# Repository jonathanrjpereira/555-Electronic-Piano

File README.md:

# Electronic Piano | LM555
An electronic piano that uses the 555 to generate eight different piano notes.

**Order PCB:**

## Electronic Components
| Qty | Component | Buy |
| ------------- | ------------- | ------------- |
| 1 | 555 |[AliExpress](http://s.click.aliexpress.com/e/sCv1ACC) |
| 1 | 390Ω, 620Ω, 910Ω, 1.1KΩ, 1.3KΩ, 1.5K, 2KΩ, 6.2KΩ |[AliExpress](http://s.click.aliexpress.com/e/bh4eqrQs) |
| 2 | 1KΩ Resistor |[AliExpress](http://s.click.aliexpress.com/e/bh4eqrQs) |
| 8 | Tactile Momentary Push Buttons |[AliExpress](http://s.click.aliexpress.com/e/c77Ajrpq) |
| 1 | 5mm LED |[AliExpress](http://s.click.aliexpress.com/e/wuFpLXS) |
| 1 | 0.1uF Capacitor |[AliExpress](http://s.click.aliexpress.com/e/c9FHzl5W) |
| 1 | 10nF Capacitor |[AliExpress](http://s.click.aliexpress.com/e/byQG0DZW) |
| 2 | 2 Pin Screw Terminal |[AliExpress](http://s.click.aliexpress.com/e/xYUweh2) |
| 1 | Speaker |[AliExpress](http://s.click.aliexpress.com/e/brMJh46c) |
| 1 | 9V Battery Holder |[AliExpress](http://s.click.aliexpress.com/e/c3jbp72Y) |
| 1 | 9V Battery |[AliExpress](http://s.click.aliexpress.com/e/bbDirGHE) |
| 1 | PCB |[AliExpress](http://s.click.aliexpress.com/e/dhgwzKY) |

| Tools | Buy |
|--|--|
|Soldering Iron|[AliExpress](http://s.click.aliexpress.com/e/E83bSJI) |
|Soldering Wire|[AliExpress](http://s.click.aliexpress.com/e/PdhB0nm) |
|Mini PCB Hand Drill + Bits|[AliExpress](http://s.click.aliexpress.com/e/b93tomjI) |

## Working
**LM555/NE555:**

The 555 is a highly stable device for generating accurate time delays or oscillation. Additional terminals are provided for triggering or resetting if desired. For stable operation as an oscillator, the free running frequency and duty cycle are accurate controlled with two external resistors and one capacitor. The circuit may be triggered and reset on falling waveforms, and he output circuit can source or sink up to 200mA or drive TTL circuits.

**Circuit:**

The circuit is connected such that it will trigger itself and free run as an astable multivibrator. The external capacitor charges through Ra+Rb and discharges through Rb. Thus th duty cycle may be precisely set by the ratio of these two resistors.

In this mode of operation, the capacitor charges and discharges between 1/3 VCC and 2/3 VCC. Hence the charge and discharge times, and therefore the frequency are independent of the supply voltage.

The change time (output high) is given by:

And the discharge time (output low) by:

Thus the total period is:

The frequency of oscillation is:

Hence

An input trigger such as a switch or button is pressed which connects its corresponding resistance within the resistor chain to the IC 555 which acts as an Astable Multivibrator. Depending on the value of the resistance the speaker will produce a different sound.

Each piano key has a separate frequency associated with it as shown in the table below.
We have kept the values of Ra & C as constant and only vary the value of Rb in order to change the frequency whenever a different key is pressed. In order to do this we created a resistor chain according to the table above as shown in the schematic. This chain is configured to optimize and reduce the number of individual resistors required.

## Contributing🛠
Are you an engineer or hobbyist who has a great idea for a new feature in this project? Maybe you have a good idea for a bug fix? Feel free to grab our code & schematics from Github and tinker with it. Don't forget to smash ⭐️ & the Pull Request button.

[![alt text][1.1]][1] [![alt text][2.1]][2] [![alt text][3.1]][3]

[1.1]: https://github.com/jonathanrjpereira/Social-Media-README/blob/master/youtube.png (YouTube)
[2.1]: https://github.com/jonathanrjpereira/Social-Media-README/blob/master/instagram.png (Instagram)
[3.1]: https://github.com/jonathanrjpereira/Social-Media-README/blob/master/github.png (GitHub)

[1]: https://www.youtube.com/channel/UCRW-41O1vy98KKgJRQoYzdg
[2]: https://www.instagram.com/electroguruji/
[3]: https://github.com/jonathanrjpereira

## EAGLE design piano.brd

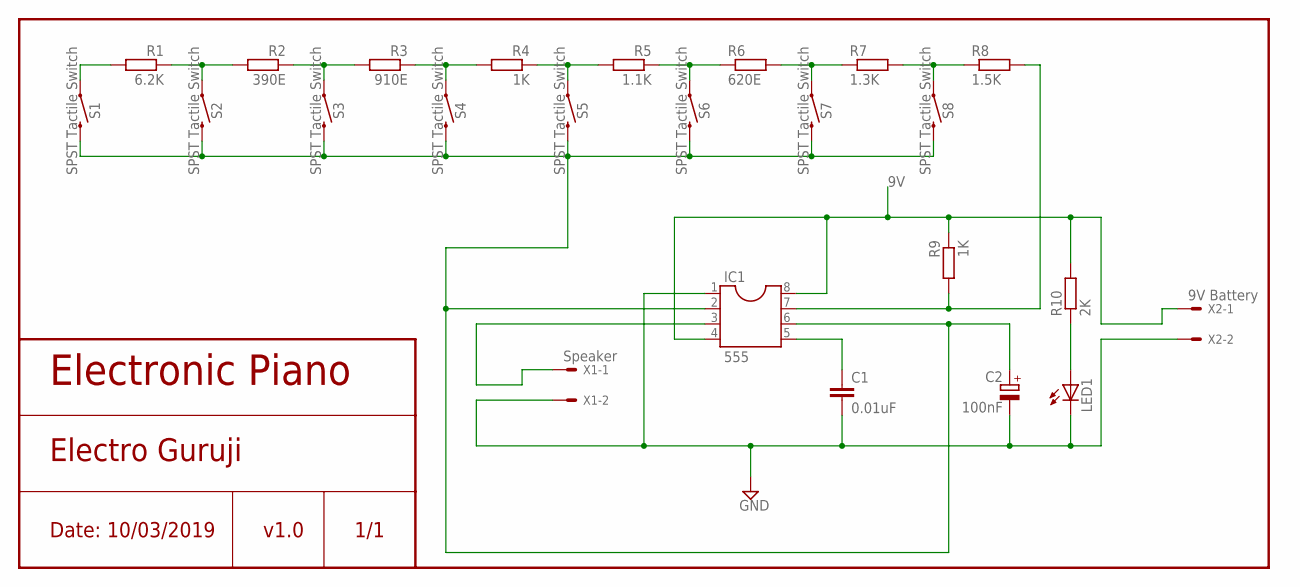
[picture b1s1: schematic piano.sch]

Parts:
C1: 0.01uF; C025-024X044
C2: 100nF; E5-5
IC1: 555; SOCKET-08
LED1: LED5MM
R1: 6.2K; 0204/5
R2: 390E; 0204/5
R3: 910E; 0204/5
R4, R9: 1K; 0204/5
R5: 1.1K; 0204/5
R6: 620E; 0204/5
R7: 1.3K; 0204/5
R8: 1.5K; 0204/5
R10: 2K; 0204/5
S1, S2, S3, S4, S5, S6, S7, S8: SPST Tactile Switch; TACTILE_SWITCH_PTH_6.0MM
X1: Speaker; KK-156-2
X2: 9V Battery; KK-156-2

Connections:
9V: IC1.4, IC1.8, R9.1, R10.2, X2.1
GND: C1.2, C2.-, IC1.1, LED1.K (C), X1.2, X2.2
unnamed: IC1.7, R8.2, R9.2
unnamed: C1.1, IC1.5
unnamed: C2.+, IC1.2, IC1.6, S1.3 (2), S2.3 (2), S3.3 (2), S4.3 (2), S5.3 (2), S6.3 (2), S7.3 (2), S8.3 (2)
unnamed: R1.2, S1.1
unnamed: R1.1, R2.2, S2.1
unnamed: R2.1, R3.2, S3.1
unnamed: R3.1, R4.2, S4.1
unnamed: R4.1, R5.2, S5.1
unnamed: R5.1, R6.1, S6.1
unnamed: R7.2, R8.1, S8.1
unnamed: R6.2, R7.1, S7.1
unnamed: IC1.3, X1.1
unnamed: LED1.A, R10.1

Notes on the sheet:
Electronic Piano
Electro Guruji
Date: 10/03/2019
v1.0
1/1

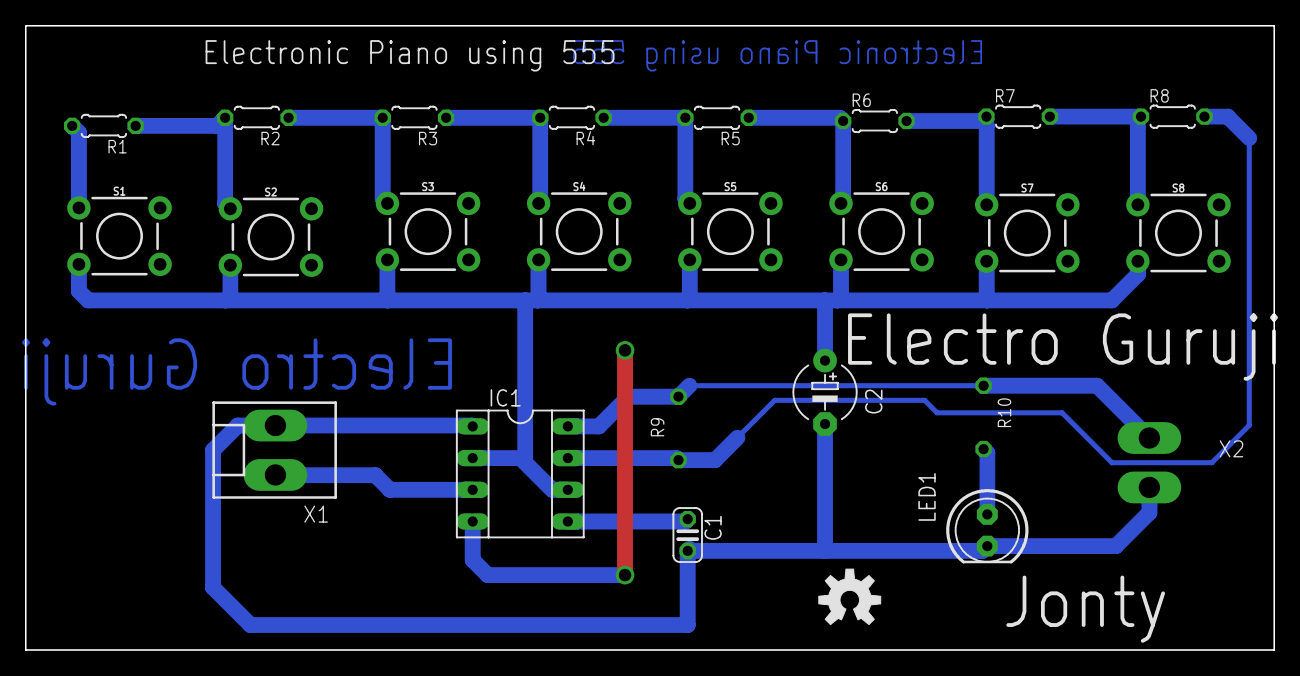
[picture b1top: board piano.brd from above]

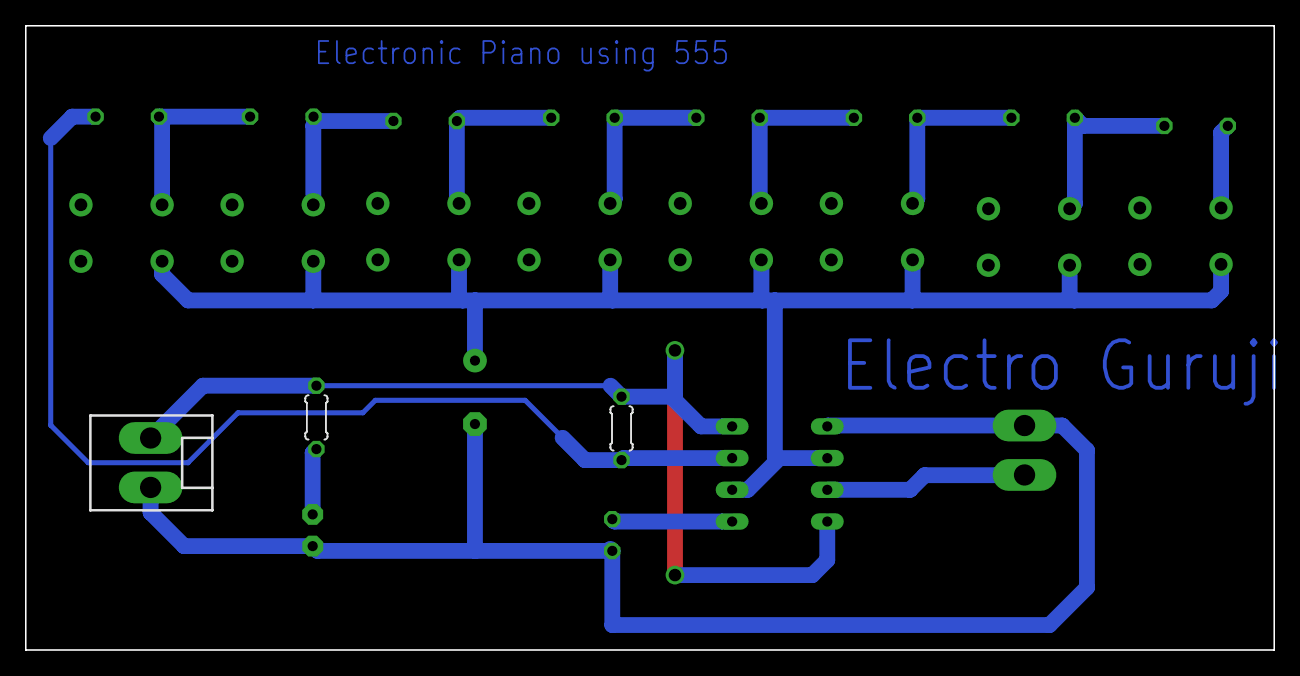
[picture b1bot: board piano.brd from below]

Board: 2 copper layers, 100.0 x 50.0 mm, 25 parts (3 on the bottom side), 15 nets.

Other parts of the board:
U$1: OSHW-LOGO-M

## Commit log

2019-03-12 All images
2019-03-12 Schematic & Board
2019-03-12 Rb Calculator
    Enter desired frequencies for fixed value of Ra & C.
    Output: Corresponding value of Rb
2019-03-12 Components, Working
2019-03-17 printable

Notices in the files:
parts and their libraries:
SparkFun-Switches: Licensing: Creative Commons ShareAlike 4.0 International - https://creativecommons.org/licenses/by-sa/4.0
